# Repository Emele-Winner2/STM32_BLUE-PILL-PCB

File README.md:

# Custom STM32F103 "Blue Pill" Development Board 🚀

This repository contains the complete hardware design files for a custom, enhanced 4-layer redesign of the classic STM32F103 "Blue Pill" development board. Designed entirely in KiCad, this board optimizes signal integrity, power distribution, and clock stability compared to standard 2-layer commercial alternatives.

---

## 🛠️ Hardware Specifications & Features

* **MCU Core:** STM32F103C8T6 ARM Cortex-M3 microcontroller.
* **4-Layer Stackup:** Engineered with dedicated internal planes to maximize electromagnetic shielding and ensure pristine signal paths.
  * **Layer 1 (Top):** High-speed signaling (USB differential pairs), crystal oscillator tracking, and local component connections.
  * **Layer 2 (Internal):** Solid, unbroken **Ground (GND) Plane** for low-impedance return paths.
  * **Layer 3 (Internal):** **Power (PWR) Plane** for clean 5V power distribution.
  * **Layer 4 (Bottom):** General purpose I/O breakouts and non-critical low-speed routing.
* **USB Interface:** Native USB Full-Speed connection with hardware-matched series termination resistors and a proper 3.3V pull-up network for reliable host computer enumeration.
* **Dual Clock Architecture:** * High-Speed External (HSE): 8MHz main crystal with optimized, short symmetric routing.
  * Low-Speed External (LSE): 32.768kHz dedicated real-time clock (RTC) crystal.

---

## 📂 Repository Structure

```text
├── bluetooth_mcu.kicad_pro   # KiCad main project file
├── bluetooth_mcu.kicad_sch   # System schematic design
├── bluetooth_mcu.kicad_pcb   # 4-layer PCB layout design
└── README.md                 # Project documentation (this file)

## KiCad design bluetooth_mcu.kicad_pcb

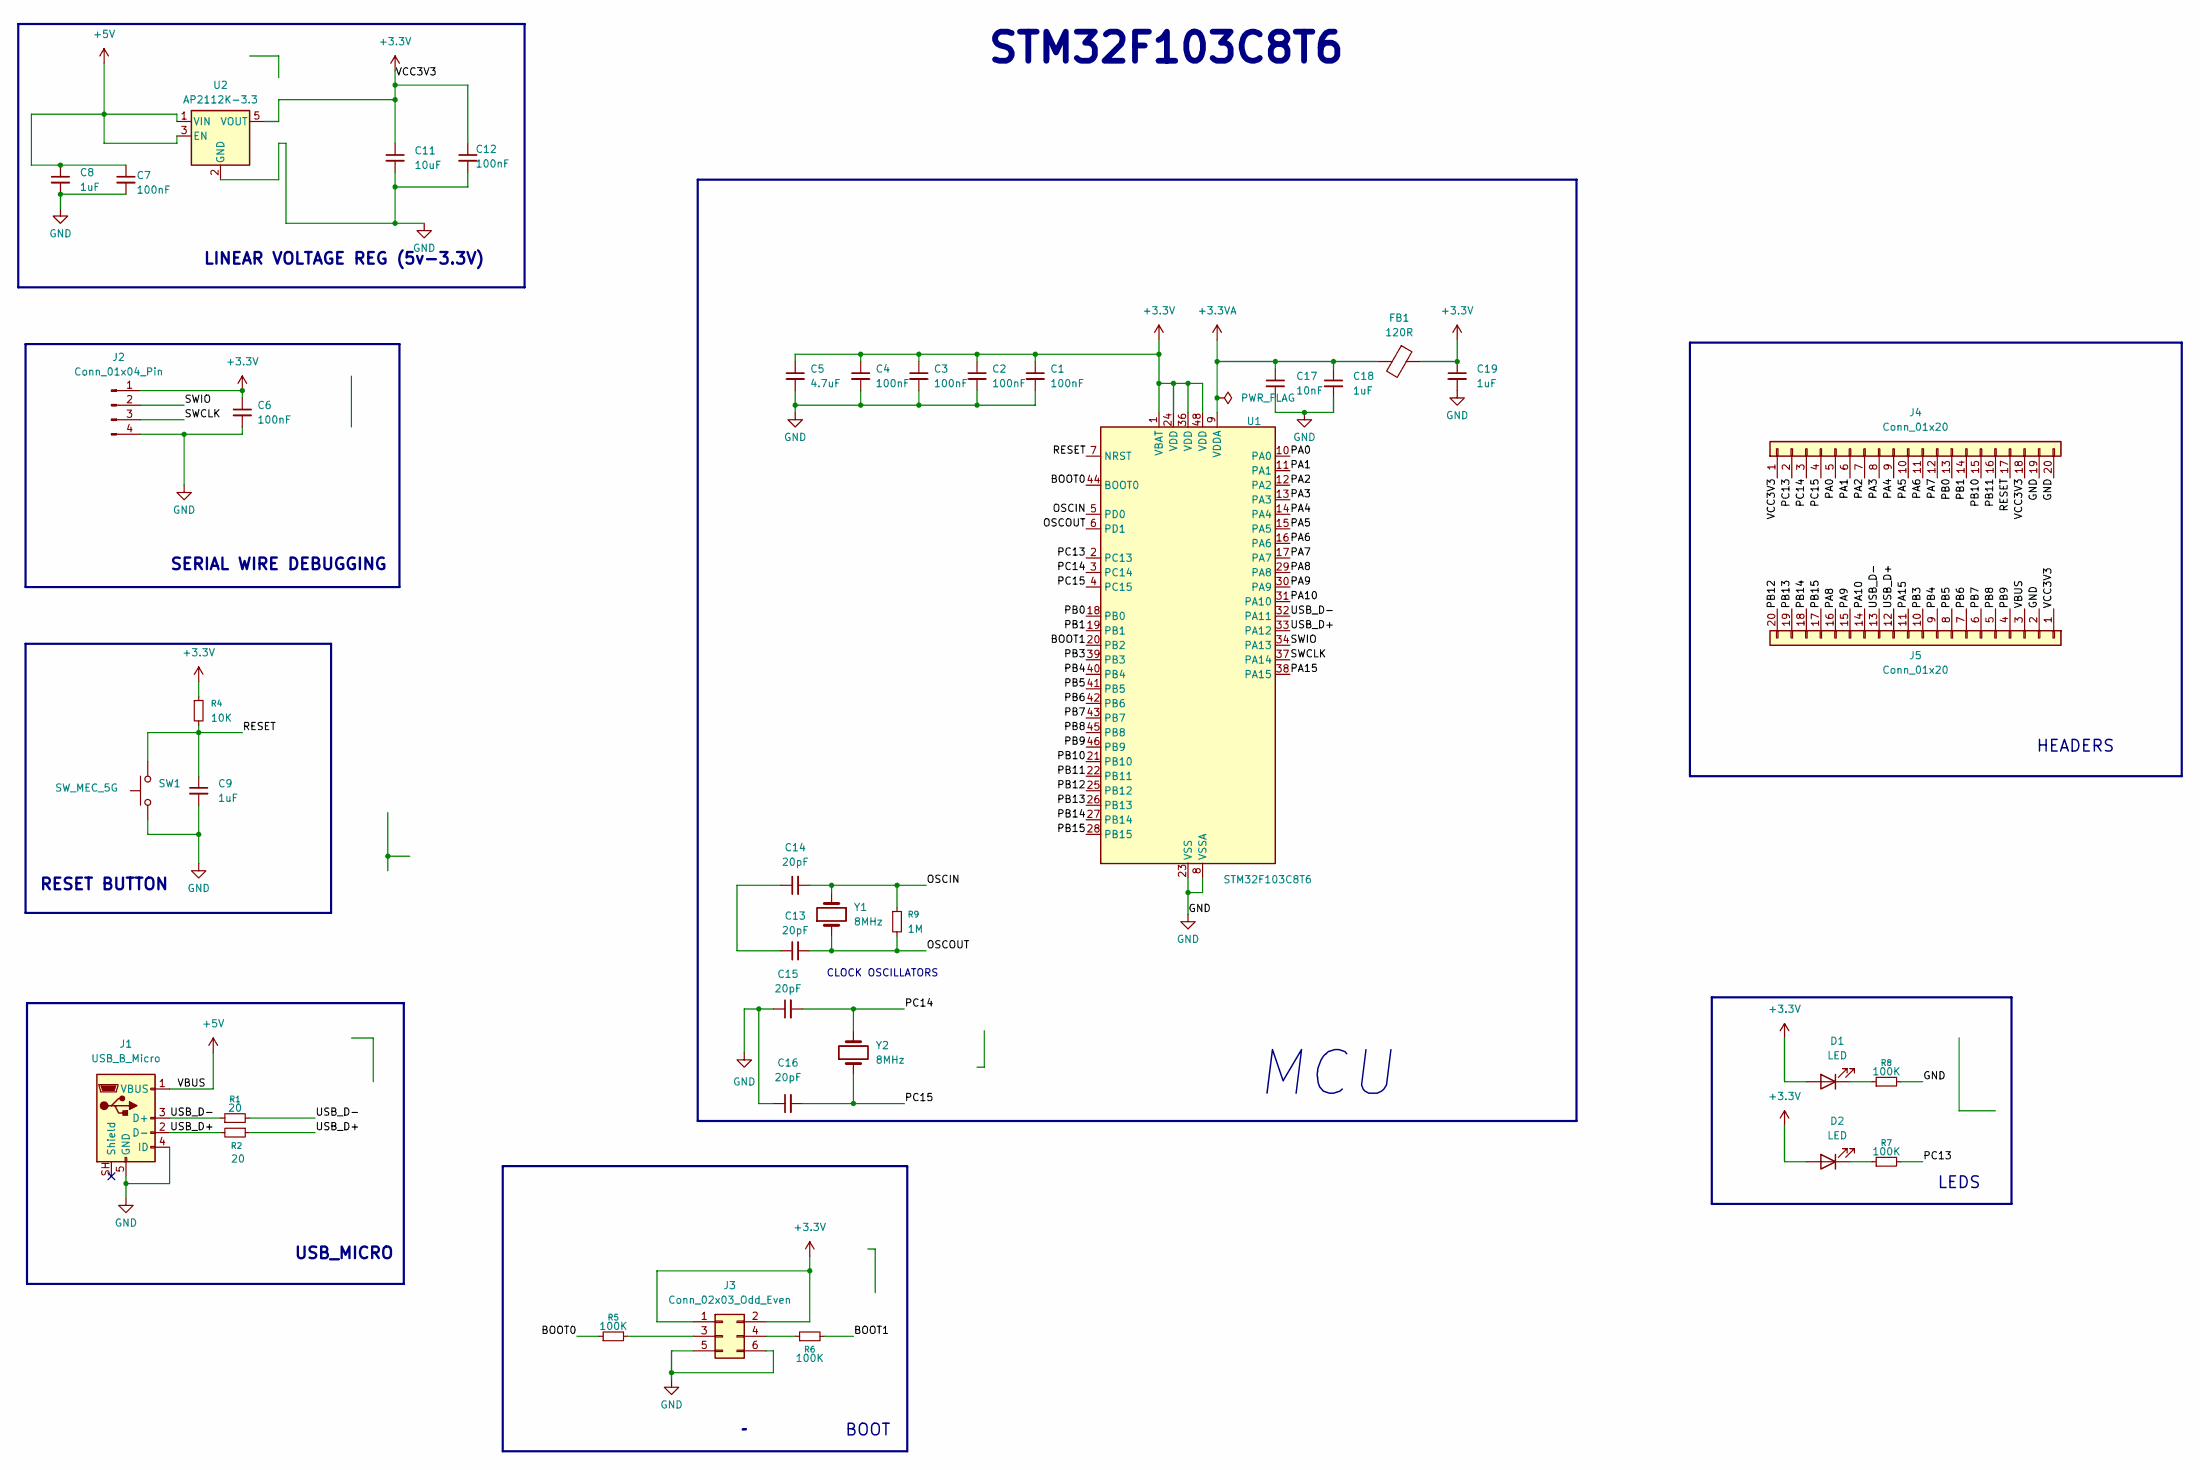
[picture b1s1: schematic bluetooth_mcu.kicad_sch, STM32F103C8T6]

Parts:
C1, C2, C3, C4, C6, C7, C12: 100nF; C_0603_1608Metric_Pad1.08x0.95mm_HandSolder
C5: 4.7uF; C_0603_1608Metric_Pad1.08x0.95mm_HandSolder
C8, C9, C18, C19: 1uF; C_0603_1608Metric_Pad1.08x0.95mm_HandSolder
C11: 10uF; C_0603_1608Metric_Pad1.08x0.95mm_HandSolder
C13, C14: 20pF; C_0402_1005Metric_Pad0.74x0.62mm_HandSolder
C15, C16: 20pF; C_0603_1608Metric_Pad1.08x0.95mm_HandSolder
C17: 10nF; C_0603_1608Metric_Pad1.08x0.95mm_HandSolder
D1, D2: LED; LED_0402_1005Metric_Pad0.77x0.64mm_HandSolder
FB1: 120R; R_0603_1608Metric
J1: USB_B_Micro; USB_Micro-B_Molex-105017-0001
J2: Conn_01x04_Pin; PinHeader_1x04_P2.54mm_Horizontal
J3: Conn_02x03_Odd_Even; PinHeader_2x03_P2.54mm_Vertical
J4, J5: Conn_01x20; PinHeader_1x20_P2.54mm_Vertical
R1, R2: 20; R_0603_1608Metric_Pad0.98x0.95mm_HandSolder
R4: 10K; R_0603_1608Metric_Pad0.98x0.95mm_HandSolder
R5, R6, R7, R8: 100K; R_0603_1608Metric_Pad0.98x0.95mm_HandSolder
R9: 1M; R_0603_1608Metric_Pad0.98x0.95mm_HandSolder
SW1: SW_MEC_5G; SW_PUSH_1P1T_6x3.5mm_H4.3_APEM_MJTP1243
U1: STM32F103C8T6; LQFP-48_7x7mm_P0.5mm
U2: AP2112K-3.3; SOT-23-5
Y1, Y2: 8MHz; Crystal_SMD_MicroCrystal_CC8V-T1A-2Pin_2.0x1.2mm_HandSolder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

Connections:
+3.3V: C1.1, C2.1, C3.1, C4.1, C5.1, C6.1, C11.1, C12.1, C19.1, D1.2 (A), D2.2 (A), FB1.1, J2.1, J3.1, J3.2, J4.1, J4.18, J5.1, R4.1, U1.1 (VBAT), U1.24 (VDD), U1.36 (VDD), U1.48 (VDD), U2.5 (VOUT)
+3.3VA: C17.1, C18.1, FB1.2, U1.9 (VDDA)
+5V: C7.1, C8.1, J1.1 (VBUS), J5.3, U2.1 (VIN), U2.3 (EN)
/BOOT0: R5.1, U1.44 (BOOT0)
/BOOT1: R6.2, U1.20 (PB2)
/OSCIN: C14.2, R9.1, U1.5 (PD0), Y1.2
/OSCOUT: C13.2, R9.2, U1.6 (PD1), Y1.1
/PA0: J4.5, U1.10 (PA0)
/PA1: J4.6, U1.11 (PA1)
/PA2: J4.7, U1.12 (PA2)
/PA3: J4.8, U1.13 (PA3)
/PA4: J4.9, U1.14 (PA4)
/PA5: J4.10, U1.15 (PA5)
/PA6: J4.11, U1.16 (PA6)
/PA7: J4.12, U1.17 (PA7)
/PA8: J5.16, U1.29 (PA8)
/PA9: J5.15, U1.30 (PA9)
/PA10: J5.14, U1.31 (PA10)
/PA15: J5.11, U1.38 (PA15)
/PB0: J4.13, U1.18 (PB0)
/PB1: J4.14, U1.19 (PB1)
/PB3: J5.10, U1.39 (PB3)
/PB4: J5.9, U1.40 (PB4)
/PB5: J5.8, U1.41 (PB5)
/PB6: J5.7, U1.42 (PB6)
/PB7: J5.6, U1.43 (PB7)
/PB8: J5.5, U1.45 (PB8)
/PB9: J5.4, U1.46 (PB9)
/PB10: J4.15, U1.21 (PB10)
/PB11: J4.16, U1.22 (PB11)
/PB12: J5.20, U1.25 (PB12)
/PB13: J5.19, U1.26 (PB13)
/PB14: J5.18, U1.27 (PB14)
/PB15: J5.17, U1.28 (PB15)
/PC13: J4.2, R7.2, U1.2 (PC13)
/PC14: C15.2, J4.3, U1.3 (PC14), Y2.2
/PC15: C16.2, J4.4, U1.4 (PC15), Y2.1
/SWCLK: J2.3, U1.37 (PA14)
/SWIO: J2.2, U1.34 (PA13)
/USB_D+: J1.2 (D-), J5.12, R2.1, R2.2, U1.33 (PA12)
/USB_D-: J1.3 (D+), J5.13, R1.1, R1.2, U1.32 (PA11)
unnamed: C13.1, C14.1
unnamed: D1.1 (K), R8.1
unnamed: D2.1 (K), R7.1
unnamed: J3.3, R5.2
unnamed: J3.4, R6.1

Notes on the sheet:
USB_MICRO
STM32F103C8T6
SERIAL WIRE DEBUGGING
BOOT
LINEAR VOLTAGE REG (5v-3.3V)
CLOCK OSCILLATORS
RESET BUTTON
MCU
HEADERS
LEDS

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
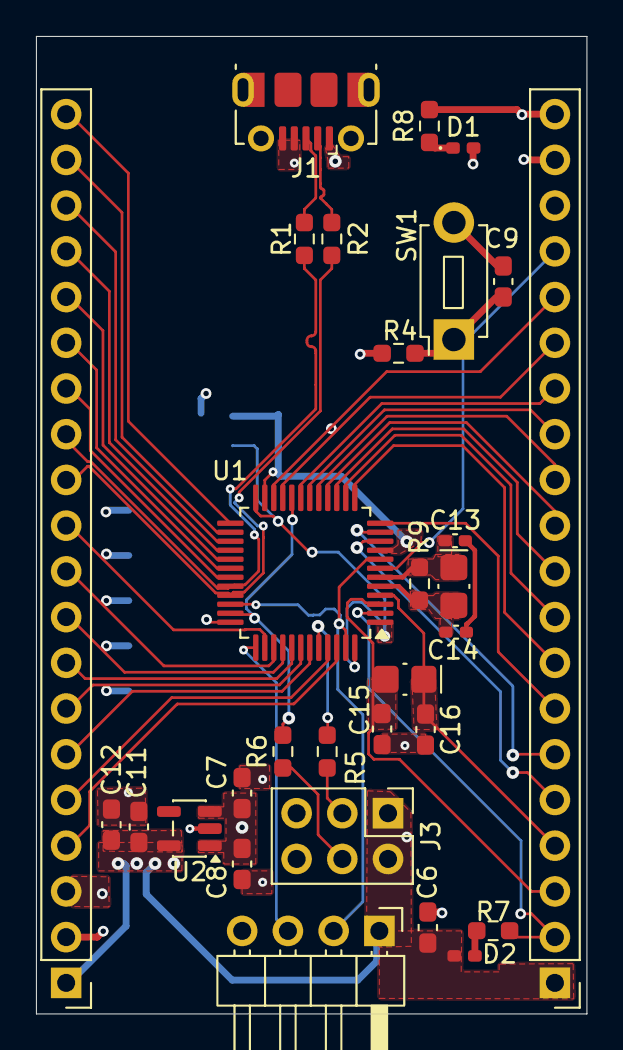
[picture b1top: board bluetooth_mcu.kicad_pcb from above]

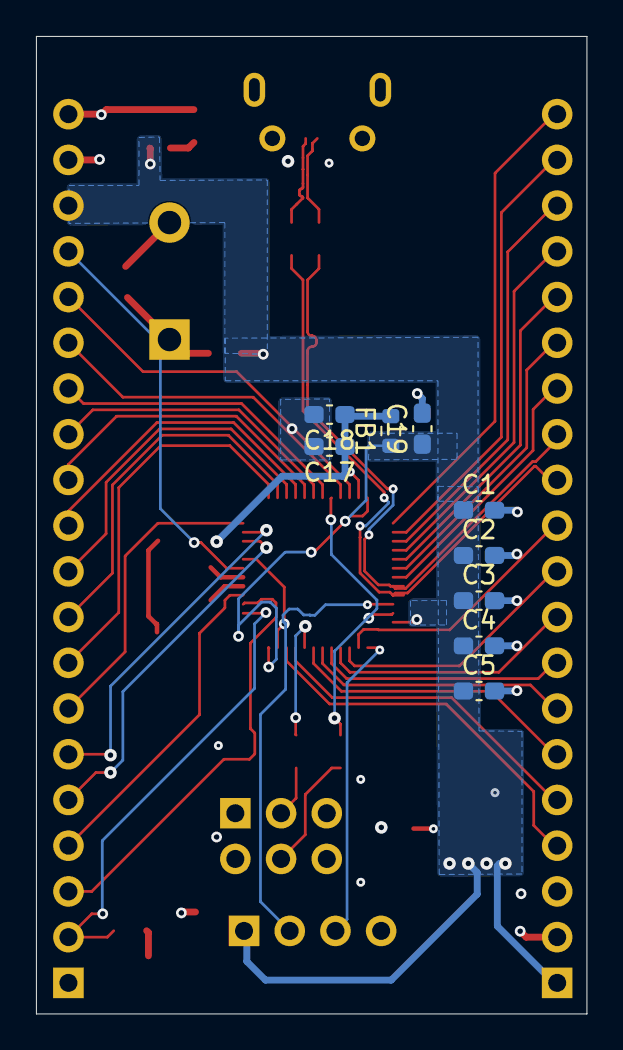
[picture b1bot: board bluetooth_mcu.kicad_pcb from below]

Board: 4 copper layers, 30.6 x 54.3 mm, 39 parts (9 on the bottom side), 48 nets.

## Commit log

2026-06-01 Update README with project details and specifications
    Added detailed project information and specifications for the custom STM32F103 'Blue Pill' development board, including hardware features and repository structure.
2026-06-01 Added files to repo
2026-06-01 Remove .gitignore from README project structure
    Remove .gitignore entry from project structure
